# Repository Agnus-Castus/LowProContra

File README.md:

# Wireless Low Profile Contra
 WIP

 notes
 Iwant to mount the Pro micro with SMD sockets like
 * 2227MC-24-06-114
 * Mac-Eight PEM-1-12P

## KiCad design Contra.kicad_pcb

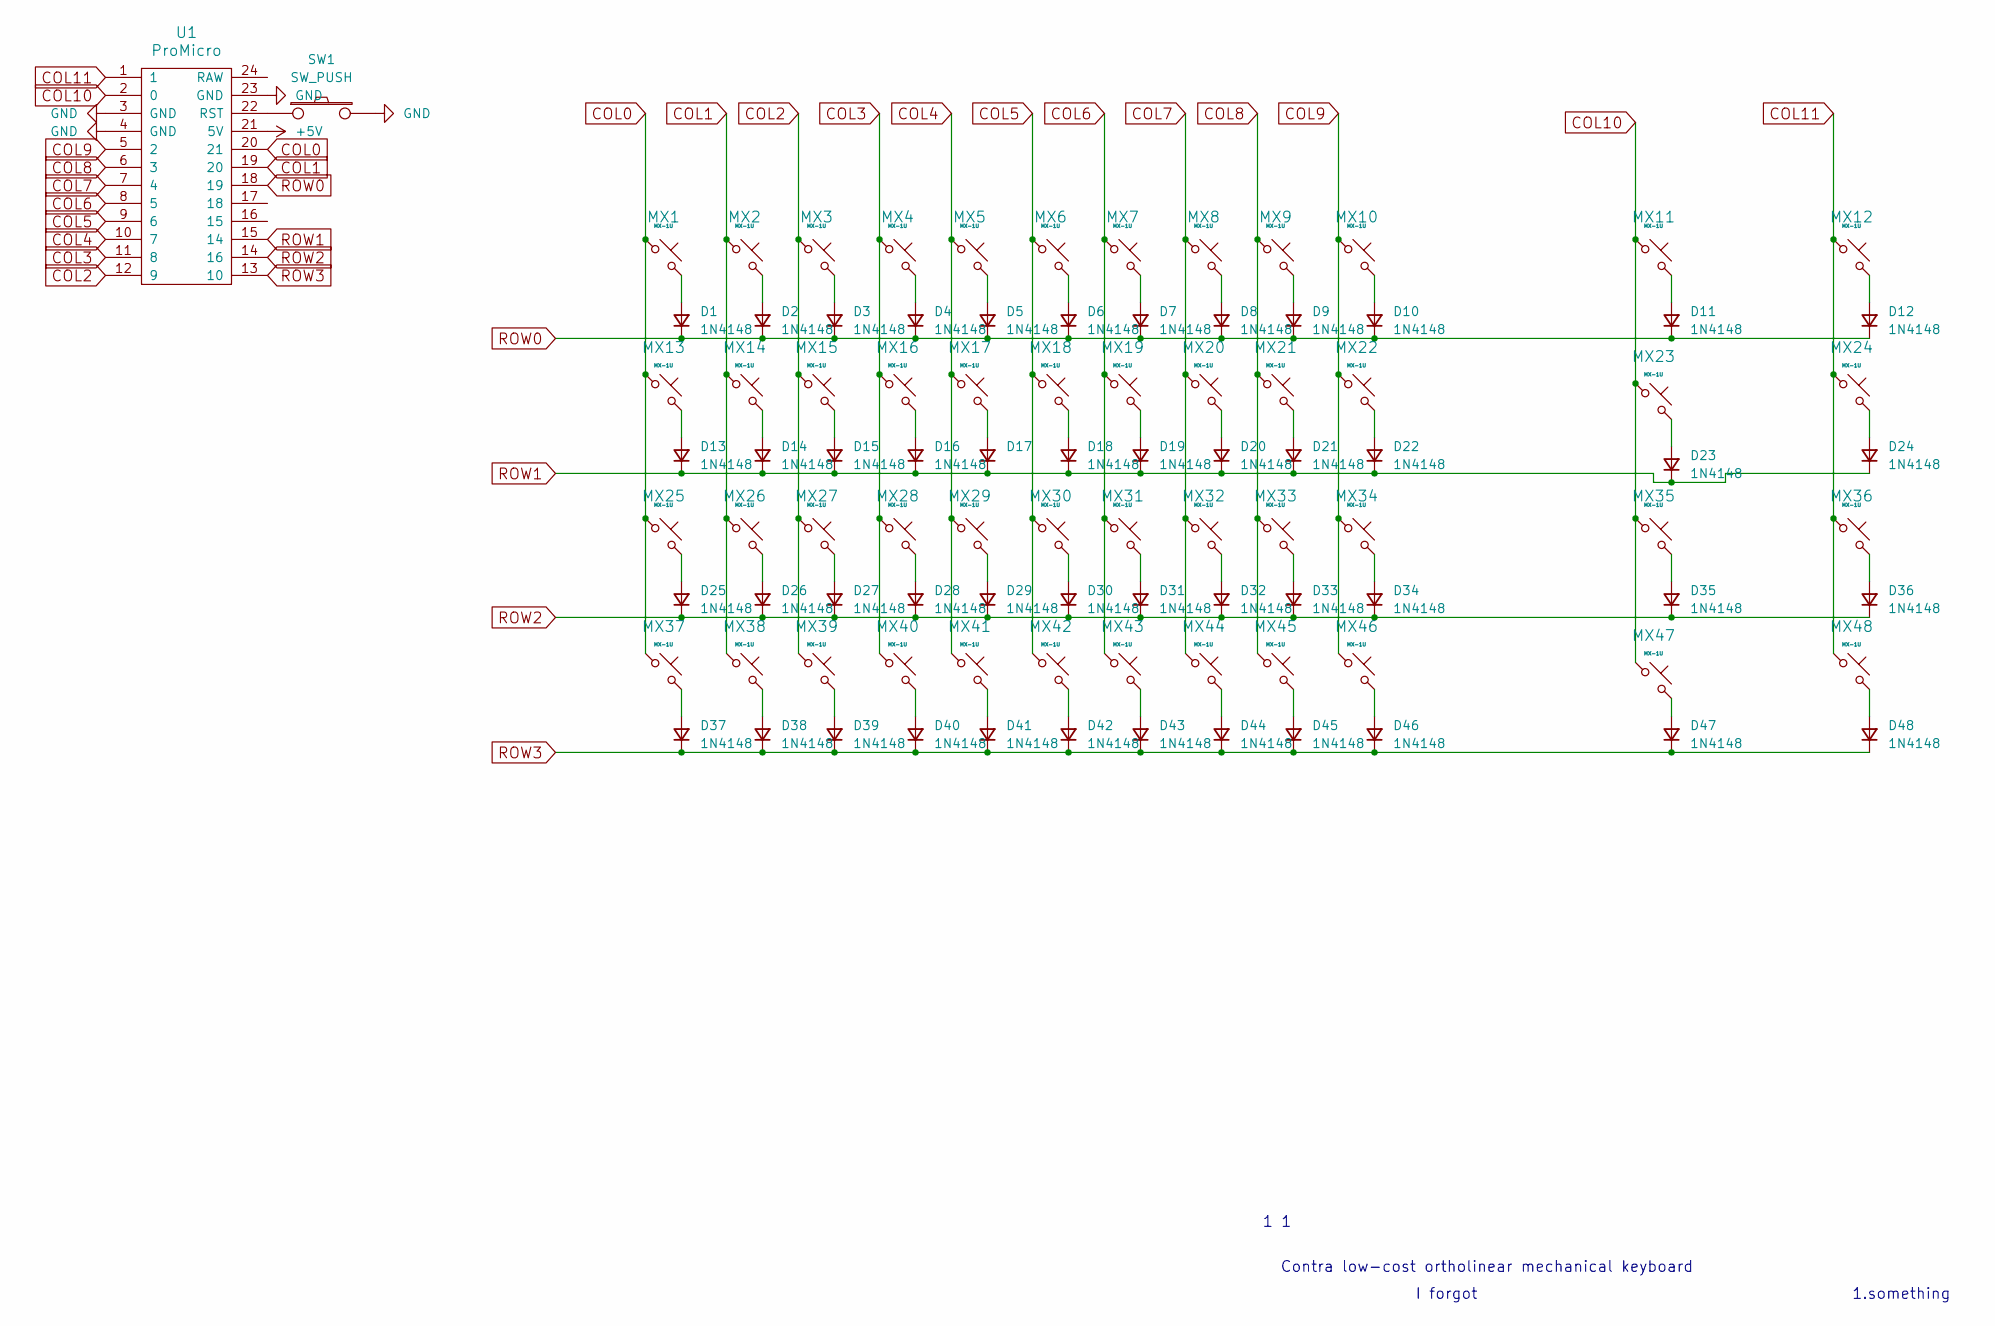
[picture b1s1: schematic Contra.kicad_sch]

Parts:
D1, D2, D3, D4, D5, D6, D7, D8, D9, D10, D11, D12, D13, D14, D15, D16, D17, D18, D19, D20, D21, D22, D23, D24, D25, D26, D27, D28, D29, D30, D31, D32, D33, D34, D35, D36, D37, D38, D39, D40, D41, D42, D43, D44, D45, D46, D47, D48: 1N4148; D_0805_2012Metric_Pad1.15x1.40mm_HandSolder
MX1, MX2, MX3, MX4, MX5, MX6, MX7, MX8, MX9, MX10, MX11, MX12, MX13, MX14, MX15, MX16, MX17, MX18, MX19, MX20, MX21, MX22, MX23, MX24, MX25, MX26, MX27, MX28, MX29, MX30, MX31, MX32, MX33, MX34, MX35, MX36, MX37, MX38, MX39, MX40, MX41, MX42, MX43, MX44, MX45, MX46, MX47, MX48: MX-1U; SW_Gateron_LowProfile_HotSwap
SW1: SW_PUSH; PushButton_6x6mm_TH_Pretty
U1: ProMicro; pro_micro

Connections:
+5V: U1.21 (5V)
COL0: MX1.1, MX13.1, MX25.1, MX37.1, U1.20 (21)
COL1: MX2.1, MX14.1, MX26.1, MX38.1, U1.19 (20)
COL2: MX3.1, MX15.1, MX27.1, MX39.1, U1.12 (9)
COL3: MX4.1, MX16.1, MX28.1, MX40.1, U1.11 (8)
COL4: MX5.1, MX17.1, MX29.1, MX41.1, U1.10 (7)
COL5: MX6.1, MX18.1, MX30.1, MX42.1, U1.9 (6)
COL6: MX7.1, MX19.1, MX31.1, MX43.1, U1.8 (5)
COL7: MX8.1, MX20.1, MX32.1, MX44.1, U1.7 (4)
COL8: MX9.1, MX21.1, MX33.1, MX45.1, U1.6 (3)
COL9: MX10.1, MX22.1, MX34.1, MX46.1, U1.5 (2)
COL10: MX11.1, MX23.1, MX35.1, MX47.1, U1.2 (0)
COL11: MX12.1, MX24.1, MX36.1, MX48.1, U1.1
GND: SW1.2, U1.3 (GND), U1.4 (GND), U1.23 (GND)
unnamed: D1.2 (A), MX1.2
unnamed: D2.2 (A), MX2.2
unnamed: D3.2 (A), MX3.2
unnamed: D4.2 (A), MX4.2
unnamed: D5.2 (A), MX5.2
unnamed: D6.2 (A), MX6.2
unnamed: D7.2 (A), MX7.2
unnamed: D8.2 (A), MX8.2
unnamed: D9.2 (A), MX9.2
unnamed: D10.2 (A), MX10.2
unnamed: D11.2 (A), MX11.2
unnamed: D12.2 (A), MX12.2
unnamed: D13.2 (A), MX13.2
unnamed: D14.2 (A), MX14.2
unnamed: D15.2 (A), MX15.2
unnamed: D16.2 (A), MX16.2
unnamed: D17.2 (A), MX17.2
unnamed: D18.2 (A), MX18.2
unnamed: D19.2 (A), MX19.2
unnamed: D20.2 (A), MX20.2
unnamed: D21.2 (A), MX21.2
unnamed: D22.2 (A), MX22.2
unnamed: D23.2 (A), MX23.2
unnamed: D24.2 (A), MX24.2
unnamed: D25.2 (A), MX25.2
unnamed: D26.2 (A), MX26.2
unnamed: D27.2 (A), MX27.2
unnamed: D28.2 (A), MX28.2
unnamed: D29.2 (A), MX29.2
unnamed: D30.2 (A), MX30.2
unnamed: D31.2 (A), MX31.2
unnamed: D32.2 (A), MX32.2
unnamed: D33.2 (A), MX33.2
unnamed: D34.2 (A), MX34.2
unnamed: D35.2 (A), MX35.2
unnamed: D36.2 (A), MX36.2
unnamed: D37.2 (A), MX37.2
unnamed: D38.2 (A), MX38.2
unnamed: D39.2 (A), MX39.2
unnamed: D40.2 (A), MX40.2
unnamed: D41.2 (A), MX41.2
unnamed: D42.2 (A), MX42.2
unnamed: D43.2 (A), MX43.2
unnamed: D44.2 (A), MX44.2
unnamed: D45.2 (A), MX45.2
unnamed: D46.2 (A), MX46.2
unnamed: D47.2 (A), MX47.2
unnamed: D48.2 (A), MX48.2
unnamed: SW1.1, U1.22 (RST)
ROW0: D1.1 (K), D2.1 (K), D3.1 (K), D4.1 (K), D5.1 (K), D6.1 (K), D7.1 (K), D8.1 (K), D9.1 (K), D10.1 (K), D11.1 (K), D12.1 (K), U1.18 (19)
ROW1: D13.1 (K), D14.1 (K), D15.1 (K), D16.1 (K), D17.1 (K), D18.1 (K), D19.1 (K), D20.1 (K), D21.1 (K), D22.1 (K), D23.1 (K), D24.1 (K), U1.15 (14)
ROW2: D25.1 (K), D26.1 (K), D27.1 (K), D28.1 (K), D29.1 (K), D30.1 (K), D31.1 (K), D32.1 (K), D33.1 (K), D34.1 (K), D35.1 (K), D36.1 (K), U1.14 (16)
ROW3: D37.1 (K), D38.1 (K), D39.1 (K), D40.1 (K), D41.1 (K), D42.1 (K), D43.1 (K), D44.1 (K), D45.1 (K), D46.1 (K), D47.1 (K), D48.1 (K), U1.13 (10)

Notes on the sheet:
Contra low-cost ortholinear mechanical keyboard
1 1
I forgot
1.something

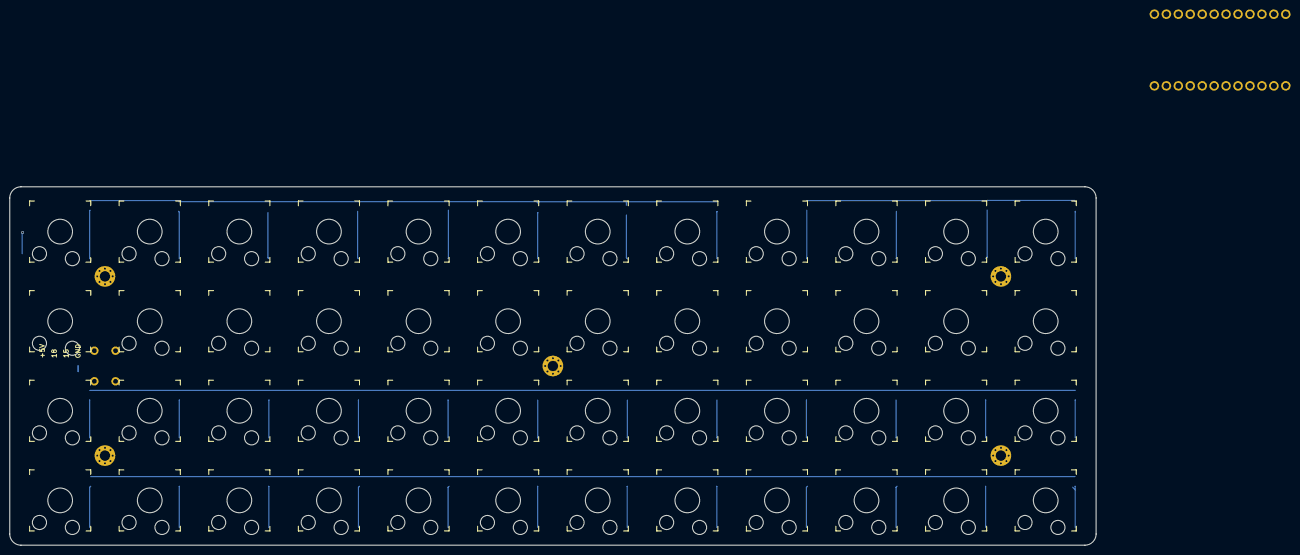
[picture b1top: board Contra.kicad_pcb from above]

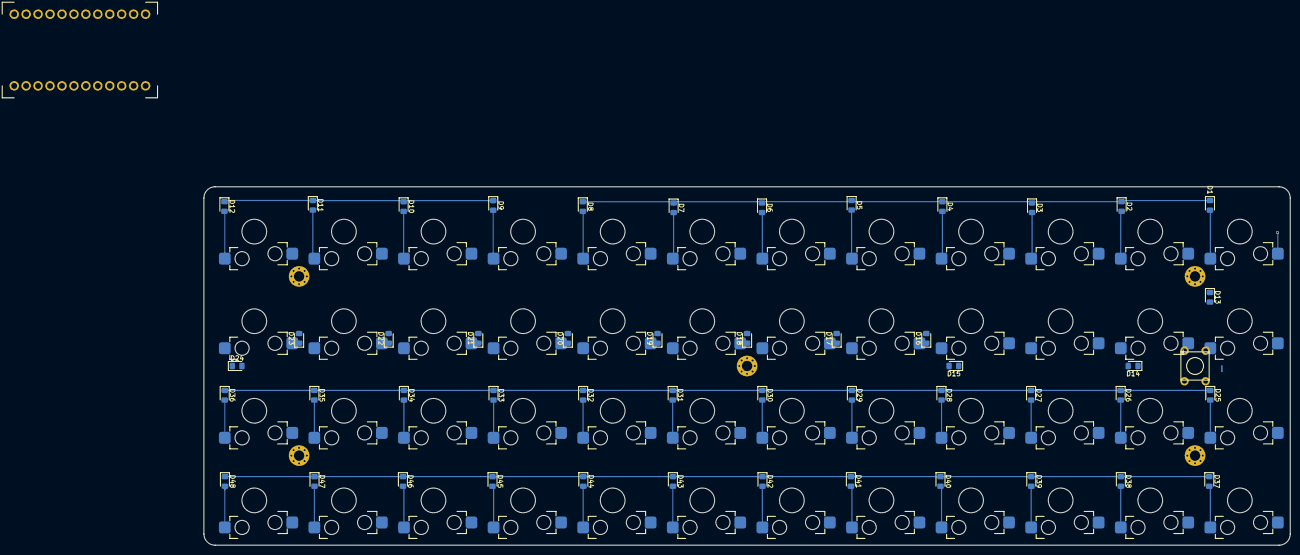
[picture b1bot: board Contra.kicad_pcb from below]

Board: 2 copper layers, 231.0 x 76.2 mm, 98 parts (50 on the bottom side), 66 nets.

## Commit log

2023-08-14 change switch symbole and migation to kicad 7
2023-08-14 Update README.md
    mark project as work in progress
2023-08-27 use smd diodes and palce on bottem select ks27 only footprint
